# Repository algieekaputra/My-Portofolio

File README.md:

# My-Portofolio

Compilation of my electronics engineering related projects

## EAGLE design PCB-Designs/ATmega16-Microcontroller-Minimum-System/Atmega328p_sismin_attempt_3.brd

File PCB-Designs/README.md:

Compilation of my PCB design projects

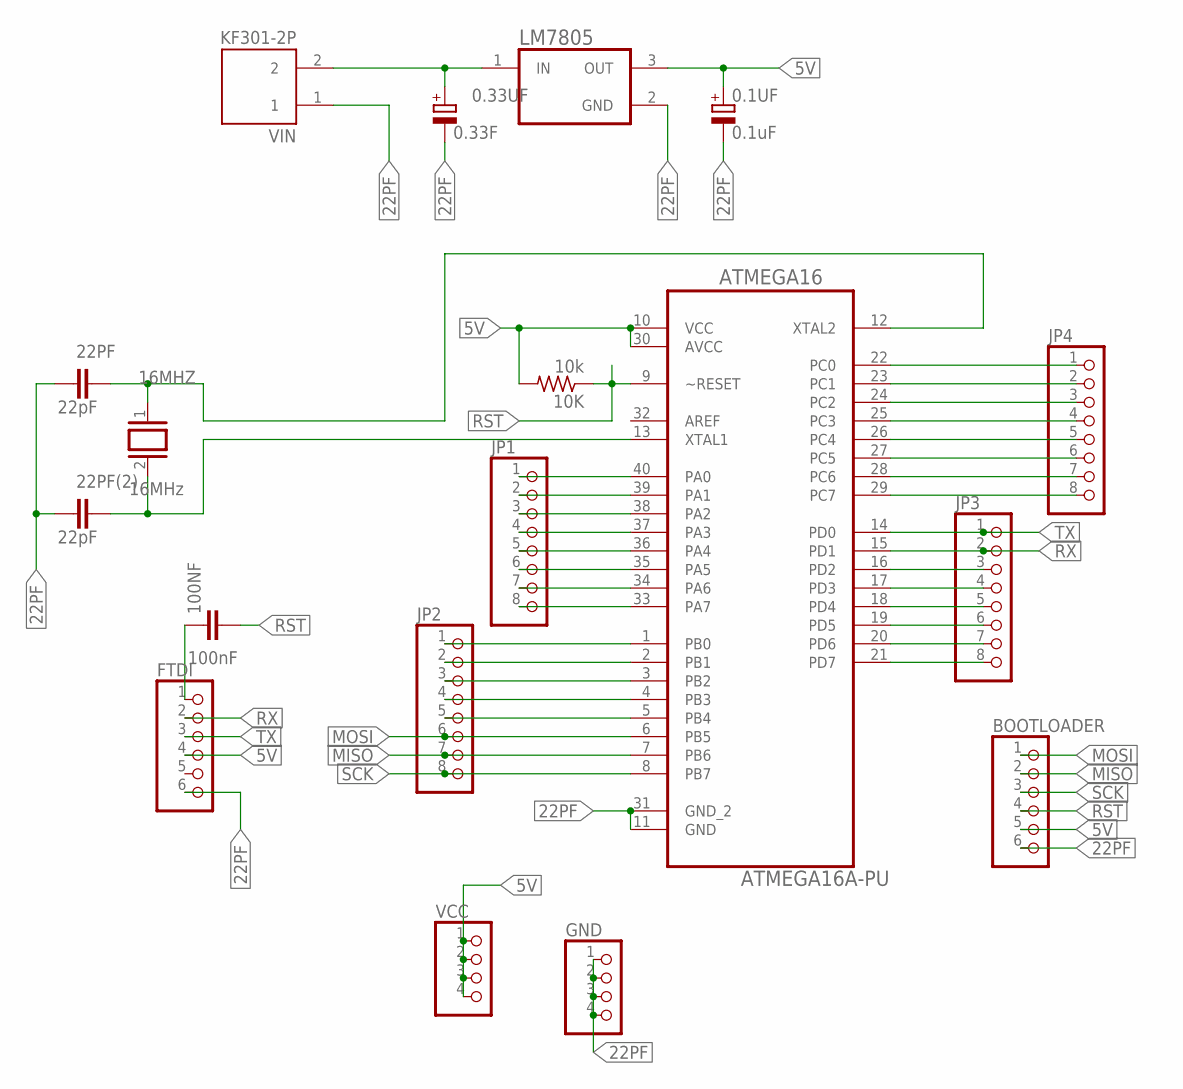
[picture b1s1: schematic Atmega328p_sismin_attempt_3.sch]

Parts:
0.1UF: 0.1uF; E2,5-6
0.33UF: 0.33F; E2,5-6
10K: 10k; 0207/7
16MHZ: 16MHz; QS
22PF, 22PF(2): 22pF; C2.5-3
100NF: 100nF; C050-025X075
ATMEGA16: ATMEGA16A-PU; DIP254P1524X482-40
BOOTLOADER: PINHD-1X6; 1X06
FTDI: PINHD-1X6; 1X06
GND: PINHD-1X4; 1X04
JP1, JP2, JP3, JP4: PINHD-1X8; 1X08
LM7805: LM7805CT/NOPB; TO254P1054X470X2600-3
VCC: PINHD-1X4; 1X04
VIN: KF301-2P; HANDSON_KF301-2P

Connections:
5V: 0.1UF.+, 10K.2, ATMEGA16.10 (VCC), ATMEGA16.30 (AVCC), BOOTLOADER.5, FTDI.4, LM7805.3 (OUT), VCC.1, VCC.2, VCC.3, VCC.4
22PF: 0.1UF.-, 0.33UF.-, 22PF.2, 22PF(2).2, ATMEGA16.11 (GND), ATMEGA16.31 (GND_2), BOOTLOADER.6, FTDI.6, GND.1, GND.2, GND.3, GND.4, LM7805.2 (GND), VIN.1
MISO: ATMEGA16.7 (PB6), BOOTLOADER.2, JP2.7
MOSI: ATMEGA16.6 (PB5), BOOTLOADER.1, JP2.6
unnamed: 16MHZ.1, 22PF.1, ATMEGA16.12 (XTAL2)
unnamed: 16MHZ.2, 22PF(2).1, ATMEGA16.13 (XTAL1)
unnamed: 0.33UF.+, LM7805.1 (IN), VIN.2
unnamed: ATMEGA16.40 (PA0), JP1.1
unnamed: ATMEGA16.39 (PA1), JP1.2
unnamed: ATMEGA16.38 (PA2), JP1.3
unnamed: ATMEGA16.37 (PA3), JP1.4
unnamed: ATMEGA16.36 (PA4), JP1.5
unnamed: ATMEGA16.35 (PA5), JP1.6
unnamed: ATMEGA16.34 (PA6), JP1.7
unnamed: ATMEGA16.33 (PA7), JP1.8
unnamed: ATMEGA16.1 (PB0), JP2.1
unnamed: ATMEGA16.2 (PB1), JP2.2
unnamed: ATMEGA16.3 (PB2), JP2.3
unnamed: ATMEGA16.4 (PB3), JP2.4
unnamed: ATMEGA16.5 (PB4), JP2.5
unnamed: ATMEGA16.22 (PC0), JP4.1
unnamed: ATMEGA16.23 (PC1), JP4.2
unnamed: ATMEGA16.24 (PC2), JP4.3
unnamed: ATMEGA16.25 (PC3), JP4.4
unnamed: ATMEGA16.26 (PC4), JP4.5
unnamed: ATMEGA16.27 (PC5), JP4.6
unnamed: ATMEGA16.28 (PC6), JP4.7
unnamed: ATMEGA16.29 (PC7), JP4.8
unnamed: ATMEGA16.16 (PD2), JP3.3
unnamed: ATMEGA16.17 (PD3), JP3.4
unnamed: ATMEGA16.18 (PD4), JP3.5
unnamed: ATMEGA16.19 (PD5), JP3.6
unnamed: ATMEGA16.20 (PD6), JP3.7
unnamed: ATMEGA16.21 (PD7), JP3.8
unnamed: 100NF.1, FTDI.1
RST: 10K.1, 100NF.2, ATMEGA16.9 (~RESET), BOOTLOADER.4
RX: ATMEGA16.15 (PD1), FTDI.2, JP3.2
SCK: ATMEGA16.8 (PB7), BOOTLOADER.3, JP2.8
TX: ATMEGA16.14 (PD0), FTDI.3, JP3.1

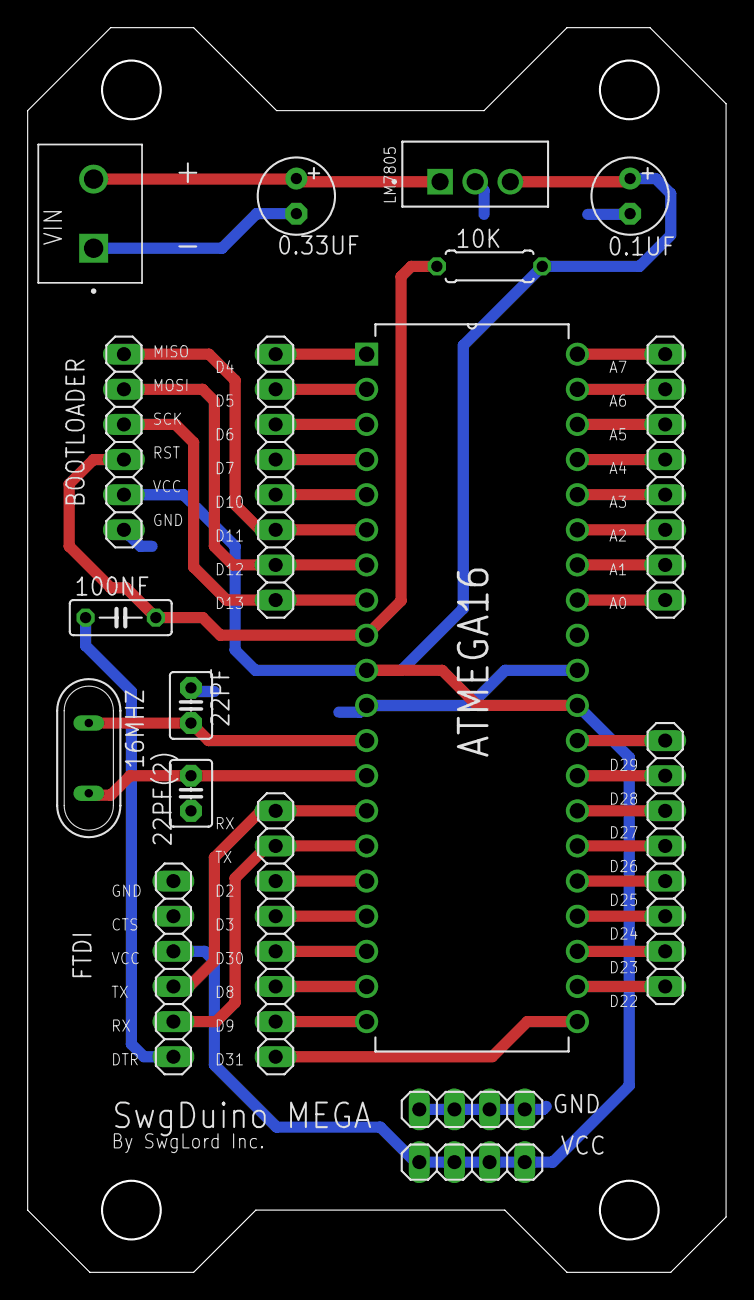
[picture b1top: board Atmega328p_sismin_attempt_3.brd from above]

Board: 2 copper layers, 50.3 x 89.8 mm, 18 parts (0 on the bottom side), 39 nets.

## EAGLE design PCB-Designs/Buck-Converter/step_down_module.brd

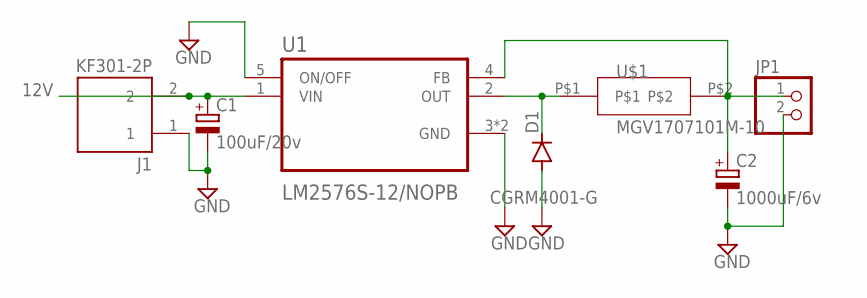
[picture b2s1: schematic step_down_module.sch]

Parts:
C1: 100uF/20v; D/7343-31W
C2: 1000uF/6v; D/7343-31W
D1: CGRM4001-G; SOD-123_MINI-SMA
J1: KF301-2P; HANDSON_KF301-2P
JP1: PINHD-1X2; 1X02
U1: LM2576S-12/NOPB; VREG_TPS79625KTTR
U$1: MGV1707101M-10

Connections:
12V: C1.+, J1.2, U1.1 (VIN)
GND: C1.-, C2.-, D1.A, J1.1, JP1.2, U1.3 (GND), U1.5 (ON/OFF), U1.6 (GND)
unnamed: D1.C, U1.2 (OUT), U$1.P$1
unnamed: C2.+, JP1.1, U1.4 (FB), U$1.P$2

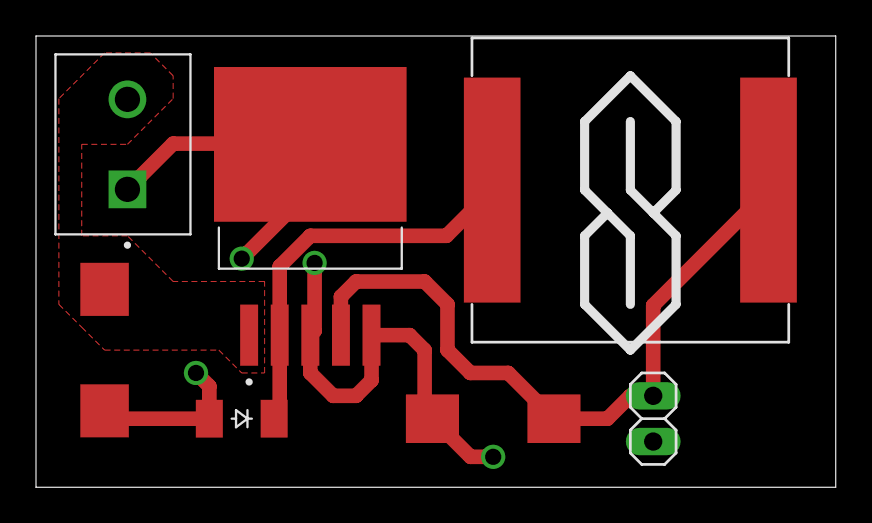
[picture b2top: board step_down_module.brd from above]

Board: 2 copper layers, 44.4 x 25.1 mm, 7 parts (0 on the bottom side), 4 nets.

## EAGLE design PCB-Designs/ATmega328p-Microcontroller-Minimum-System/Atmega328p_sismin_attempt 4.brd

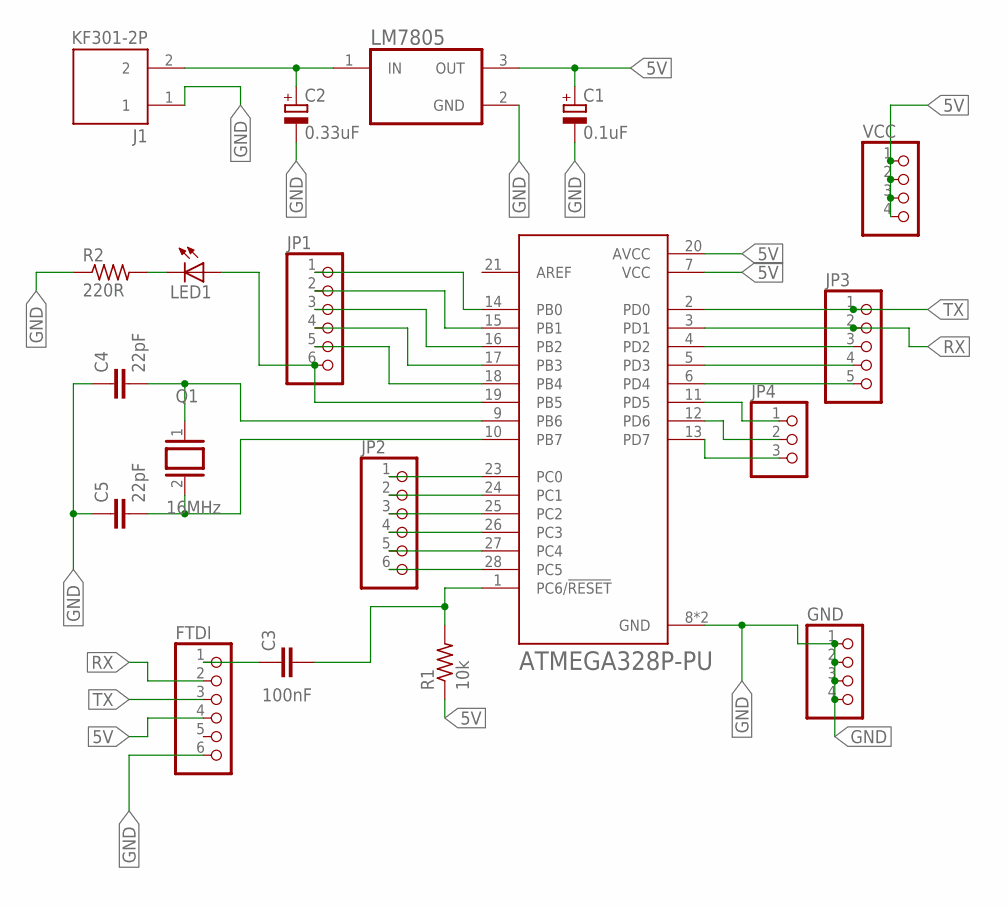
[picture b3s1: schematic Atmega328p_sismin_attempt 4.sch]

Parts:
C1: 0.1uF; E2,5-6
C2: 0.33uF; E2,5-6
C3: 100nF; C050-025X075
C4, C5: 22pF; C025-025X050
FTDI: PINHD-1X6; 1X06
GND: PINHD-1X4; 1X04
J1: KF301-2P; HANDSON_KF301-2P
JP1, JP2: PINHD-1X6; 1X06
JP3: PINHD-1X5; 1X05
JP4: PINHD-1X3; 1X03
LED1: LED5MM
LM7805: LM7805CT/NOPB; TO254P1054X470X2600-3
Q1: 16MHz; QS
R1: 10k; 0207/7
R2: 220R; 0204/7
U1: ATMEGA328P-PU; DIP794W46P254L2967H457Q28B
VCC: PINHD-1X4; 1X04

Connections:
5V: C1.+, FTDI.4, LM7805.3 (OUT), R1.1, U1.7 (VCC), U1.20 (AVCC), VCC.1, VCC.2, VCC.3, VCC.4
GND: C1.-, C2.-, C4.1, C5.1, FTDI.6, GND.1, GND.2, GND.3, GND.4, J1.1, LM7805.2 (GND), R2.1, U1.8 (GND), U1.22 (GND)
unnamed: C4.2, Q1.1, U1.9 (PB6)
unnamed: C5.2, Q1.2, U1.10 (PB7)
unnamed: C2.+, J1.2, LM7805.1 (IN)
unnamed: C3.1, FTDI.1
unnamed: C3.2, R1.2, U1.1 (PC6/!RESET)
unnamed: JP1.1, U1.14 (PB0)
unnamed: JP1.2, U1.15 (PB1)
unnamed: JP1.3, U1.16 (PB2)
unnamed: JP1.4, U1.17 (PB3)
unnamed: JP1.5, U1.18 (PB4)
unnamed: JP1.6, LED1.A, U1.19 (PB5)
unnamed: LED1.K (C), R2.2
unnamed: JP3.3, U1.4 (PD2)
unnamed: JP3.4, U1.5 (PD3)
unnamed: JP3.5, U1.6 (PD4)
unnamed: JP4.1, U1.11 (PD5)
unnamed: JP4.2, U1.12 (PD6)
unnamed: JP4.3, U1.13 (PD7)
unnamed: JP2.1, U1.23 (PC0)
unnamed: JP2.2, U1.24 (PC1)
unnamed: JP2.3, U1.25 (PC2)
unnamed: JP2.4, U1.26 (PC3)
unnamed: JP2.5, U1.27 (PC4)
unnamed: JP2.6, U1.28 (PC5)
RX: FTDI.2, JP3.2, U1.3 (PD1)
TX: FTDI.3, JP3.1, U1.2 (PD0)

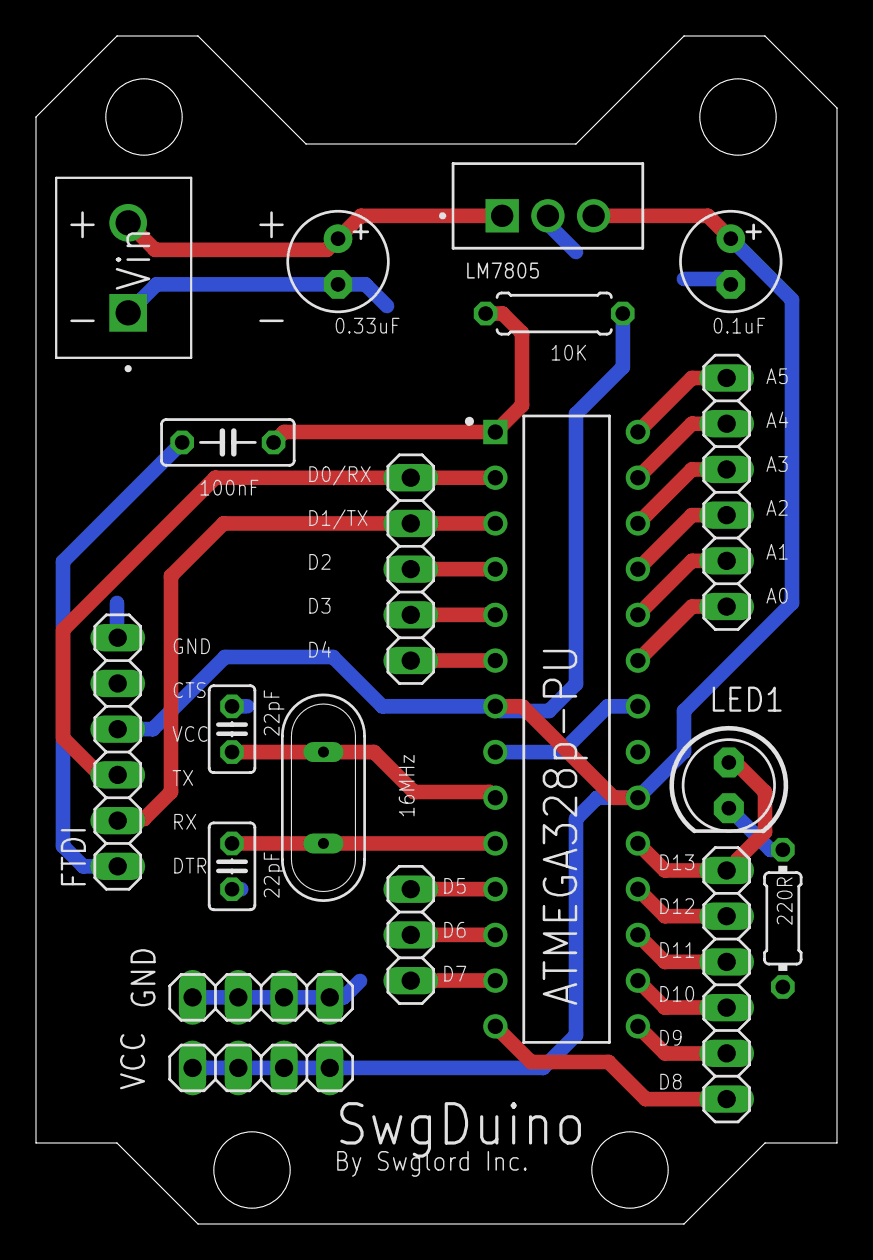
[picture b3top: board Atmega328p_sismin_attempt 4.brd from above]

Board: 2 copper layers, 44.5 x 66.0 mm, 19 parts (0 on the bottom side), 28 nets.

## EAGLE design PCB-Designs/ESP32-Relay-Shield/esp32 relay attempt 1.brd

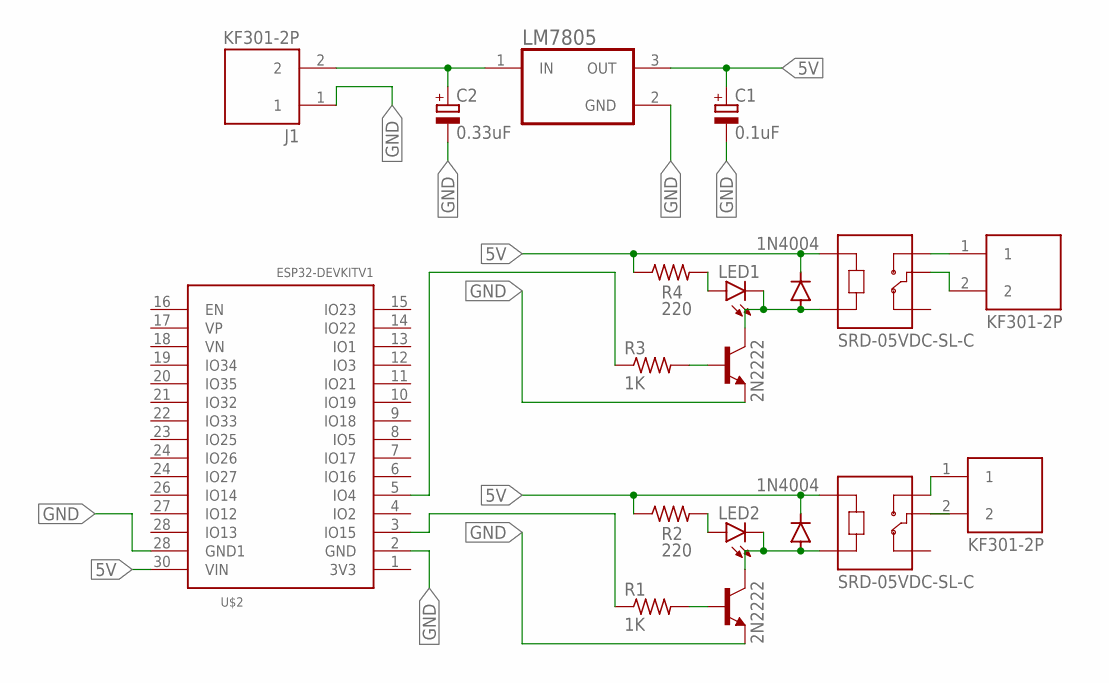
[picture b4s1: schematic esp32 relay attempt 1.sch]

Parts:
C1: 0.1uF; E2,5-6
C2: 0.33uF; E2,5-6
D1, D2: 1N4004; DO41-10
J1, J2, J3: KF301-2P; HANDSON_KF301-2P
K1, K2: SRD-05VDC-SL-C; RELAY_SRD-05VDC-SL-C
LED1, LED2: LED5MM
LM7805: LM7805CT/NOPB; TO254P1054X470X2600-3
R1, R3: 1K; 0204/7
R2, R4: 220; 0204/7
T1, T2: 2N2222; TO92-EBC-OVAL
U$2: ESP32DEVKITV1; ESP32-DEVKITV1

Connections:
5V: C1.+, D1.C, D2.C, K1.A1, K2.A1, LM7805.3 (OUT), R2.1, R4.1, U$2.30 (VIN)
GND: C1.-, C2.-, J1.1, LM7805.2 (GND), T1.E, T2.E, U$2.2 (GND), U$2.28 (IO13)
unnamed: J2.1, K1.NO
unnamed: J2.2, K1.COM
unnamed: C2.+, J1.2, LM7805.1 (IN)
unnamed: D1.A, K1.A2, LED1.K (C), T1.C
unnamed: R3.2, T1.B
unnamed: R3.1, U$2.5 (IO4)
unnamed: LED1.A, R4.2
unnamed: J3.1, K2.NO
unnamed: J3.2, K2.COM
unnamed: D2.A, K2.A2, LED2.K (C), T2.C
unnamed: R1.2, T2.B
unnamed: R1.1, U$2.3 (IO15)
unnamed: LED2.A, R2.2

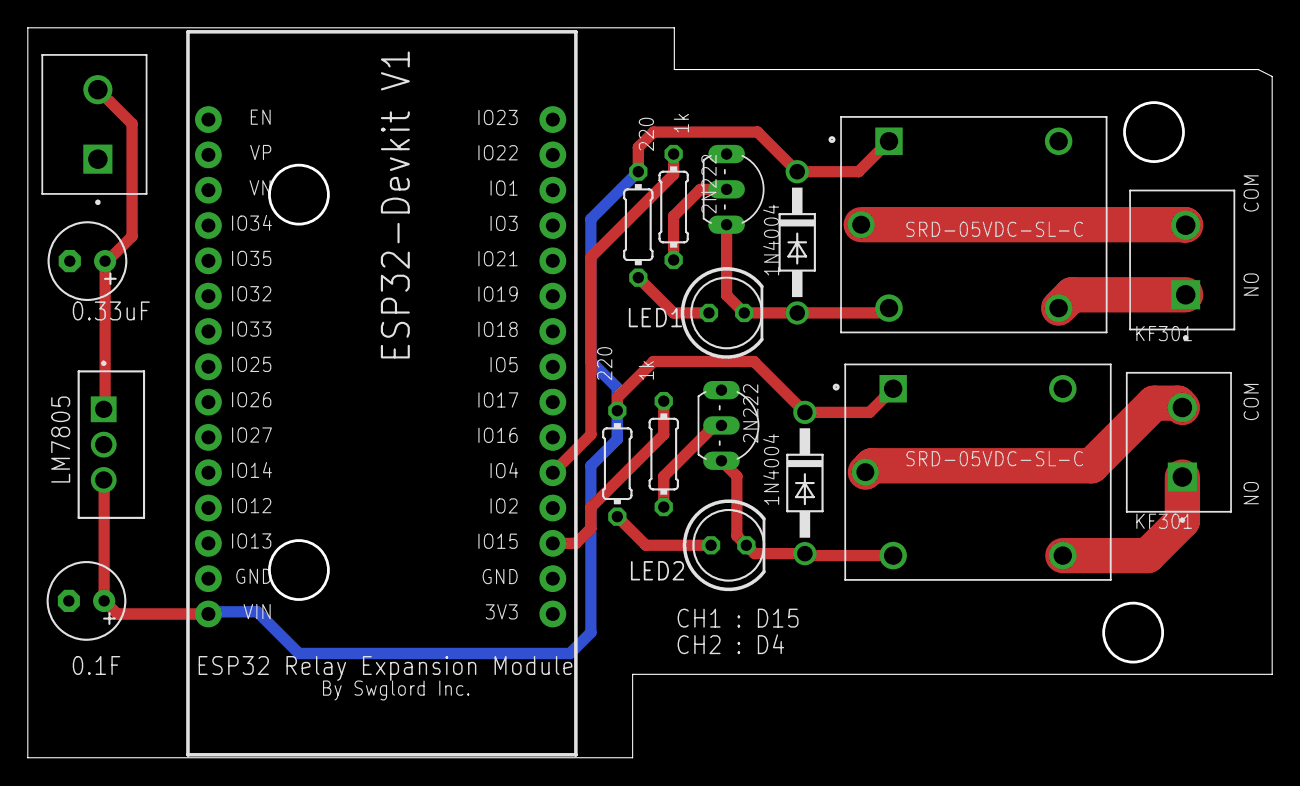
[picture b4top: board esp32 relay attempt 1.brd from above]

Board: 2 copper layers, 89.3 x 52.3 mm, 19 parts (0 on the bottom side), 15 nets.

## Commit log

2024-03-09 Create README.md
    Compilations of my PCB design projects
2024-03-09 Create README.md
    PCB design of two-channel relay shield for ESP32
2024-03-09 Create README.md
    Compilation of my embedded systems related projects
